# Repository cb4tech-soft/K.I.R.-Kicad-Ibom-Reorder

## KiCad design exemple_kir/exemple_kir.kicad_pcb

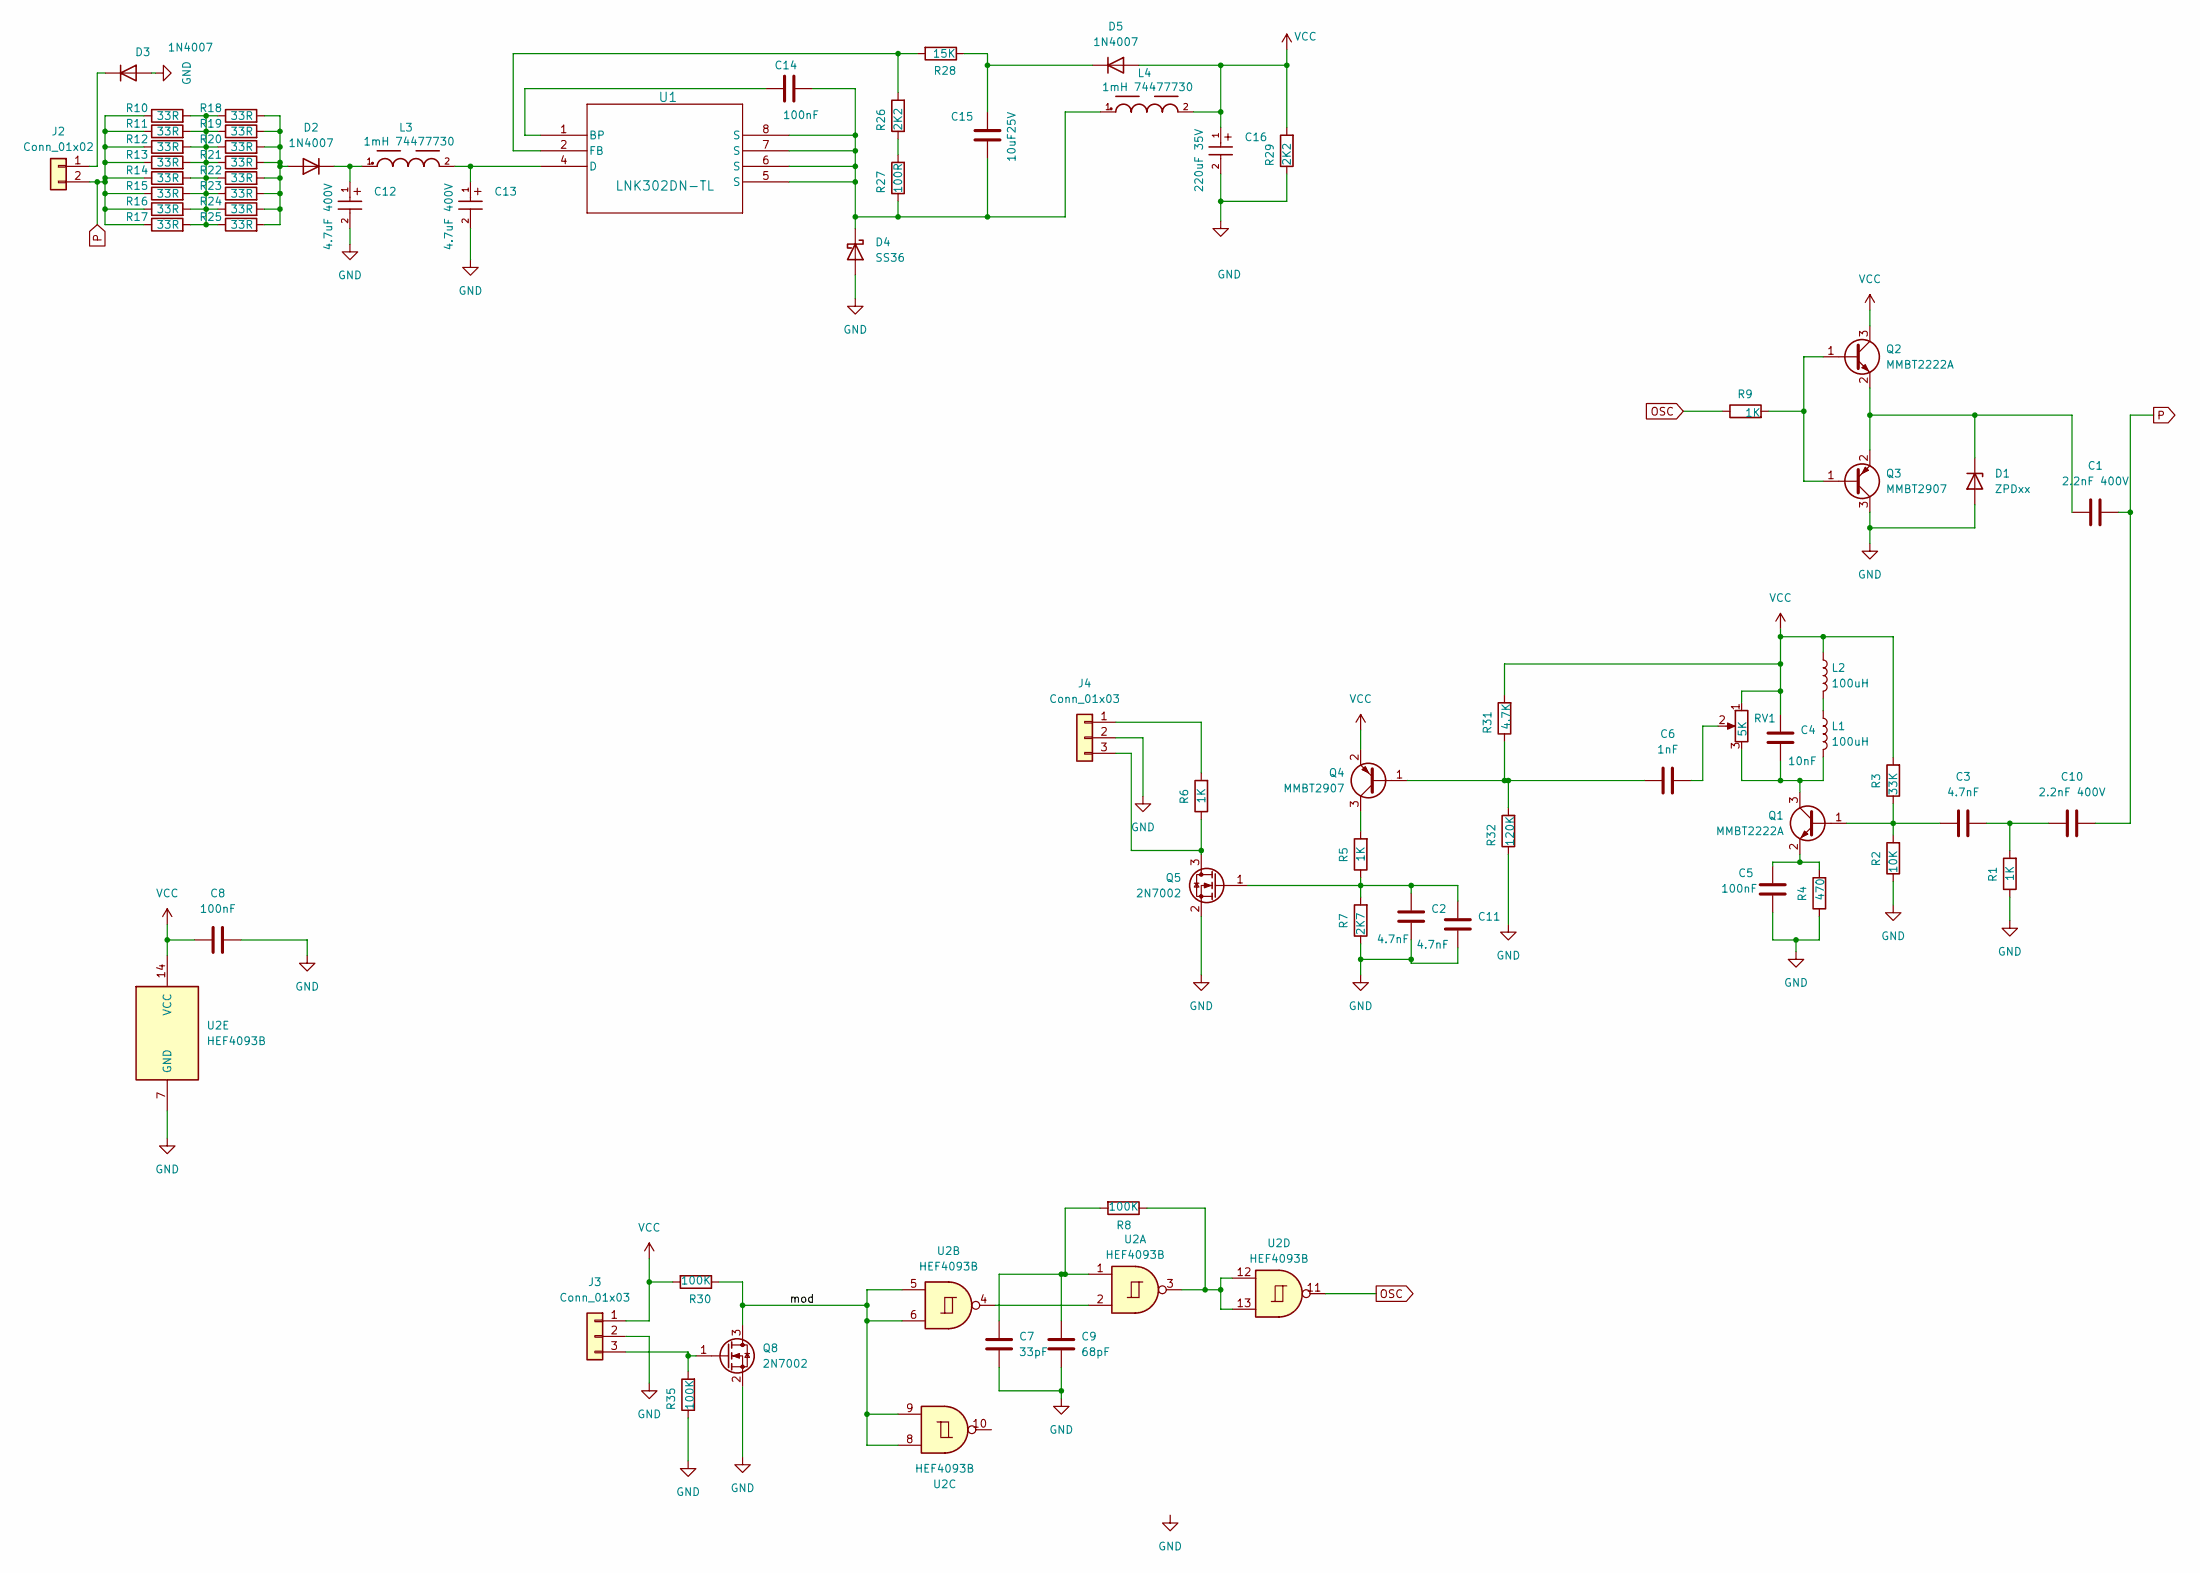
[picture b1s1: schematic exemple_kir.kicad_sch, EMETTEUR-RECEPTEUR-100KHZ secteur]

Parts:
C1, C10: 2.2nF 400V; C_1812_4532Metric_Pad1.57x3.40mm_HandSolder
C2, C3, C11: 4.7nF; C_0805_2012Metric_Pad1.18x1.45mm_HandSolder
C4: 10nF; C_0805_2012Metric_Pad1.18x1.45mm_HandSolder
C5, C8, C14: 100nF; C_0805_2012Metric_Pad1.18x1.45mm_HandSolder
C6: 1nF; C_0805_2012Metric_Pad1.18x1.45mm_HandSolder
C7: 33pF; C_0805_2012Metric_Pad1.18x1.45mm_HandSolder
C9: 68pF; C_0805_2012Metric_Pad1.18x1.45mm_HandSolder
C12, C13: 4.7uF 400V; WCAP-ATG8_8X11.5_DXL_
C15: 10uF25V; C_1206_3216Metric_Pad1.33x1.80mm_HandSolder
C16: 220uF 35V; WCAP-ATG8_8X11.5_DXL_
D1: ZPDxx; D_DO-35_SOD27_P10.16mm_Horizontal
D2, D3, D5: 1N4007; D_DO-41_SOD81_P10.16mm_Horizontal
D4: SS36; D_SMA
J2: Conn_01x02; TerminalBlock_bornier-2_P5.08mm
J3, J4: Conn_01x03; PinHeader_1x03_P2.54mm_Vertical
L1, L2: 100uH; L_Axial_L9.5mm_D4.0mm_P2.54mm_Vertical_Fastron_SMCC
L3, L4: 1mH 74477730; WE-PD_7345P
Q1, Q2: MMBT2222A; SOT-23
Q3, Q4: MMBT2907; SOT-23
Q5, Q8: 2N7002; SOT-23
R1, R5, R6, R9: 1K; R_0805_2012Metric_Pad1.20x1.40mm_HandSolder
R2: 10K; R_0805_2012Metric_Pad1.20x1.40mm_HandSolder
R3: 33K; R_0805_2012Metric_Pad1.20x1.40mm_HandSolder
R4: 470; R_0805_2012Metric_Pad1.20x1.40mm_HandSolder
R7: 2K7; R_0805_2012Metric_Pad1.20x1.40mm_HandSolder
R8, R30, R35: 100K; R_0805_2012Metric_Pad1.20x1.40mm_HandSolder
R10, R11, R12, R13, R14, R15, R16, R17, R18, R19, R20, R21, R22, R23, R24, R25: 33R; R_Axial_DIN0207_L6.3mm_D2.5mm_P10.16mm_Horizontal
R26, R29: 2K2; R_0805_2012Metric_Pad1.20x1.40mm_HandSolder
R27: 100R; R_0805_2012Metric_Pad1.20x1.40mm_HandSolder
R28: 15K; R_0805_2012Metric_Pad1.20x1.40mm_HandSolder
R31: 4.7K; R_0805_2012Metric_Pad1.20x1.40mm_HandSolder
R32: 120K; R_0805_2012Metric_Pad1.20x1.40mm_HandSolder
RV1: 5K; Potentiometer_ACP_CA6-H2,5_Horizontal
U1: LNK302DN-TL; SOIC7_SO-8C-D_PWI
U2: HEF4093B; CERDIP-14_W7.62mm_SideBrazed_LongPads_Socket

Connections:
/mod: Q8.3 (D), R30.1, U2.5, U2.6, U2.8, U2.9
GND: C2.1, C5.1, C7.1, C8.1, C9.1, C11.1, C12.2, C13.2, C16.2, D1.2 (A), D3.2 (A), D4.2 (A), J3.2, J4.2, Q3.3 (C), Q5.2 (S), Q8.2 (S), R1.1, R2.1, R4.1, R7.1, R29.1, R32.1, R35.1, U2.7 (GND)
unnamed: C6.2, RV1.2
unnamed: C7.2, C9.2, R8.2, U2.1
unnamed: C3.2, C10.1, R1.2
unnamed: C1.1, D1.1 (K), Q2.2 (E), Q3.2 (E)
unnamed: D2.2 (A), R18.2, R19.2, R20.2, R21.2, R22.2, R23.2, R24.2, R25.2
unnamed: C12.1, D2.1 (K), L3.1
unnamed: D3.1 (K), J2.1
unnamed: C14.1, C15.1, D4.1 (K), L4.1, R27.1, U1.5 (S), U1.6 (S), U1.7 (S), U1.8 (S)
unnamed: C15.2, D5.1 (K), R28.1
unnamed: J3.3, Q8.1 (G), R35.2
unnamed: J4.1, R6.2
unnamed: J4.3, Q5.3 (D), R6.1
unnamed: L1.1, L2.2
unnamed: C3.1, Q1.1 (B), R2.2, R3.1
unnamed: C4.1, L1.2, Q1.3 (C), RV1.3
unnamed: C5.2, Q1.2 (E), R4.2
unnamed: Q2.1 (B), Q3.1 (B), R9.2
unnamed: C6.1, Q4.1 (B), R31.1, R32.2
unnamed: Q4.3 (C), R5.2
unnamed: C2.2, C11.2, Q5.1 (G), R5.1, R7.2
unnamed: R8.1, U2.3, U2.12, U2.13
unnamed: R10.2, R11.2, R12.2, R13.2, R14.2, R15.2, R16.2, R17.2, R18.1, R19.1, R20.1, R21.1, R22.1, R23.1, R24.1, R25.1
unnamed: R26.1, R27.2
unnamed: C14.2, U1.1 (BP)
unnamed: C13.1, L3.2, U1.4 (D)
unnamed: R26.2, R28.2, U1.2 (FB)
unnamed: U2.2, U2.4
OSC: R9.1, U2.11
P: C1.2, C10.2, J2.2, R10.1, R11.1, R12.1, R13.1, R14.1, R15.1, R16.1, R17.1
VCC: C4.2, C8.2, C16.1, D5.2 (A), J3.1, L2.1, L4.2, Q2.3 (C), Q4.2 (E), R3.2, R29.2, R30.2, R31.2, RV1.1, U2.14 (VCC)

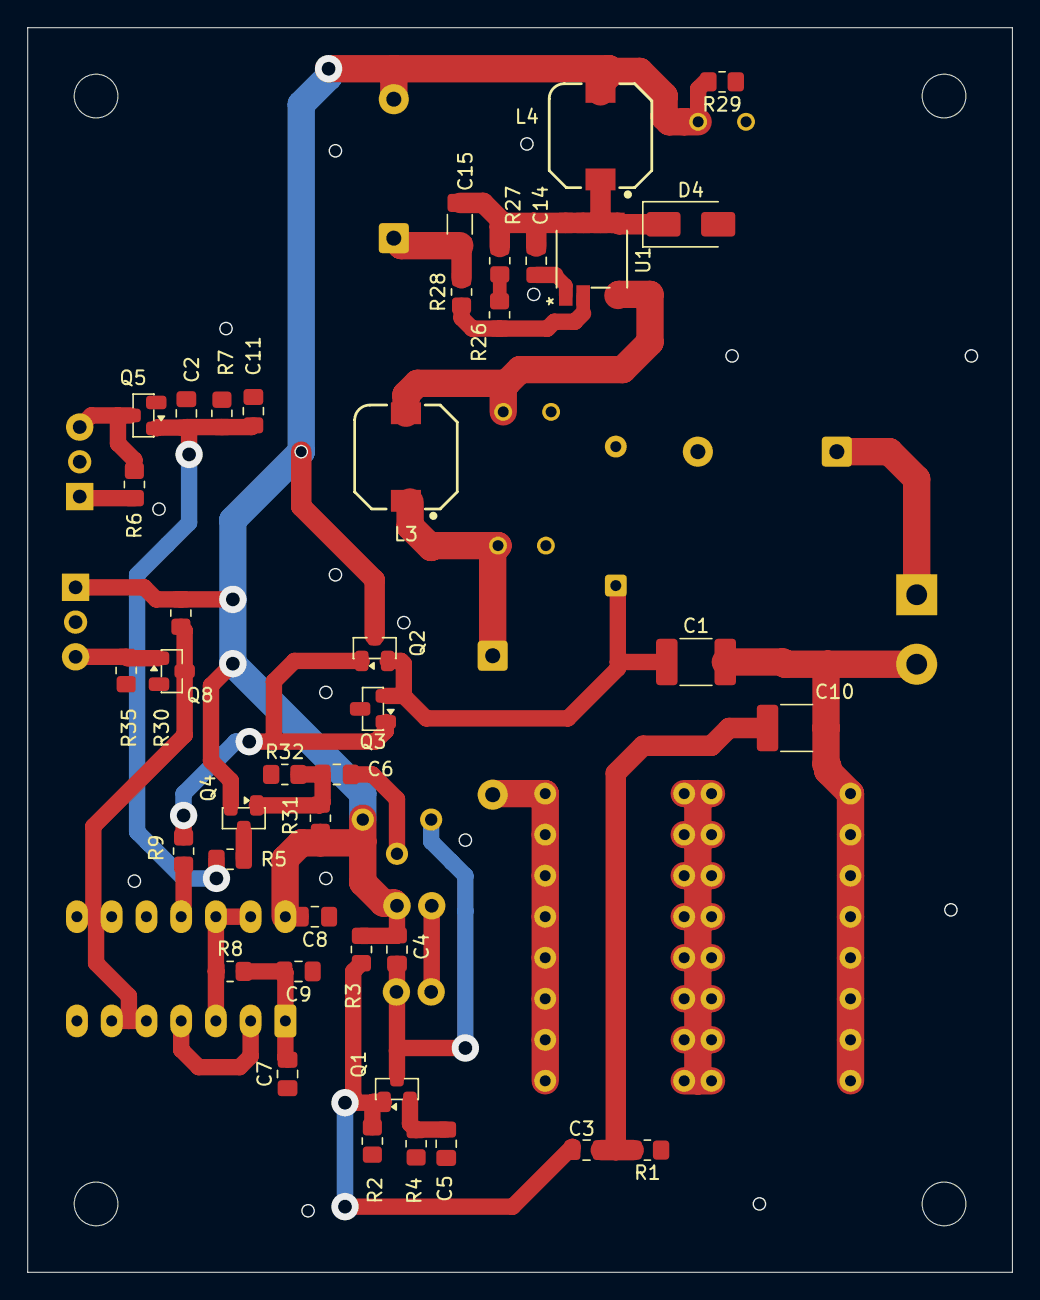
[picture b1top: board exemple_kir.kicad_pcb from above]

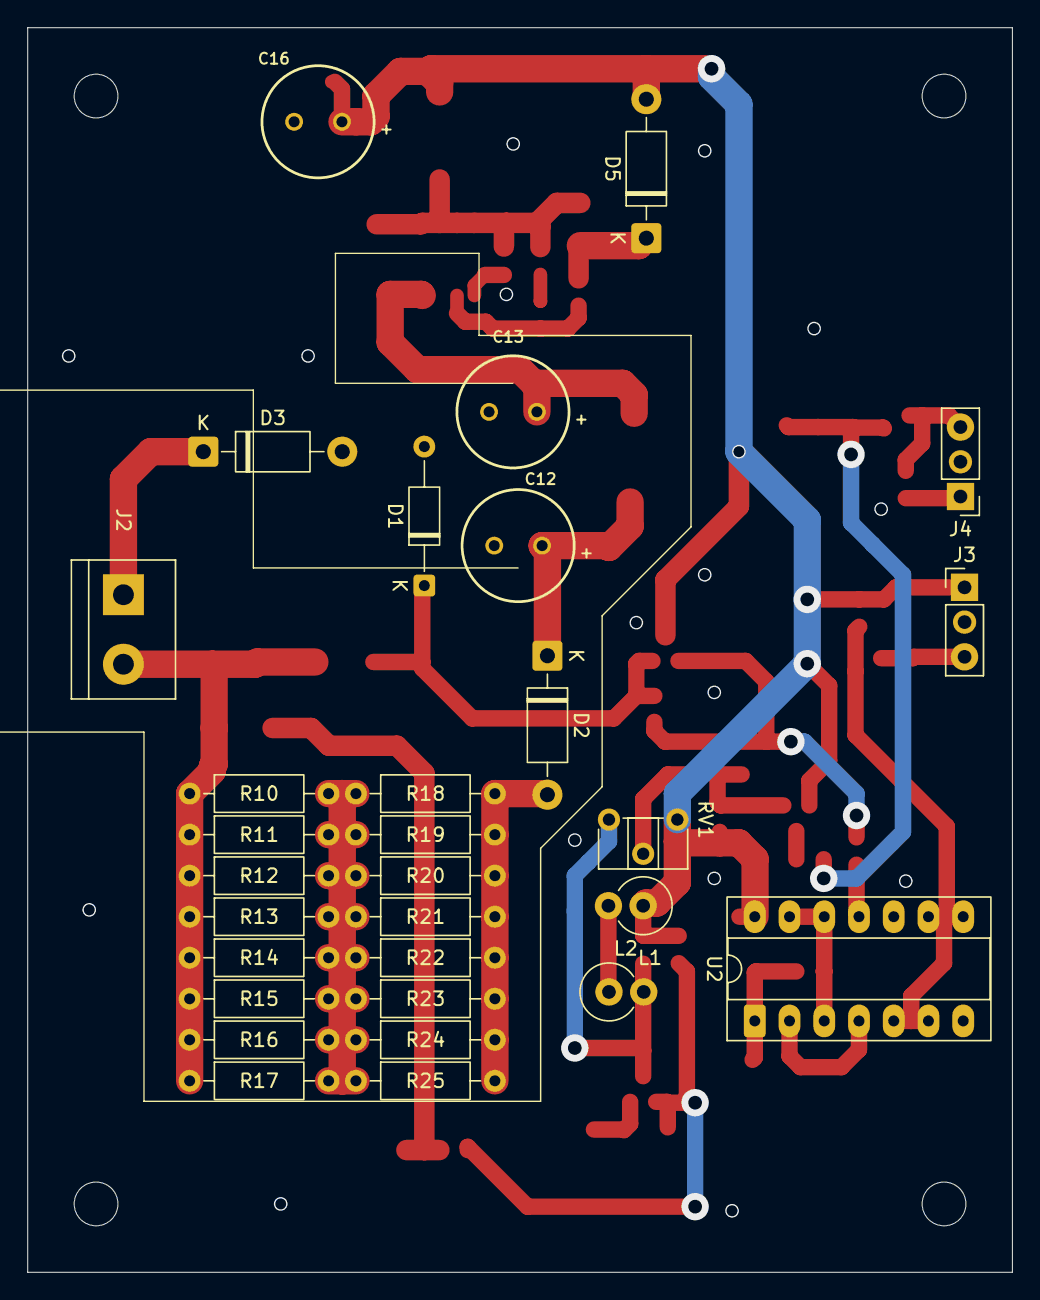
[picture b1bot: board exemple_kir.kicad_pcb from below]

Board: 2 copper layers, 72.0 x 91.0 mm, 70 parts (30 on the bottom side), 32 nets.

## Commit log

2026-01-26 Add file kir and bom
2026-01-26 Update project name in README
2026-02-04 preaparation PWA
2026-02-11 remove exemple folder
2026-02-11 remove license and readme
2026-02-18 update exemple
